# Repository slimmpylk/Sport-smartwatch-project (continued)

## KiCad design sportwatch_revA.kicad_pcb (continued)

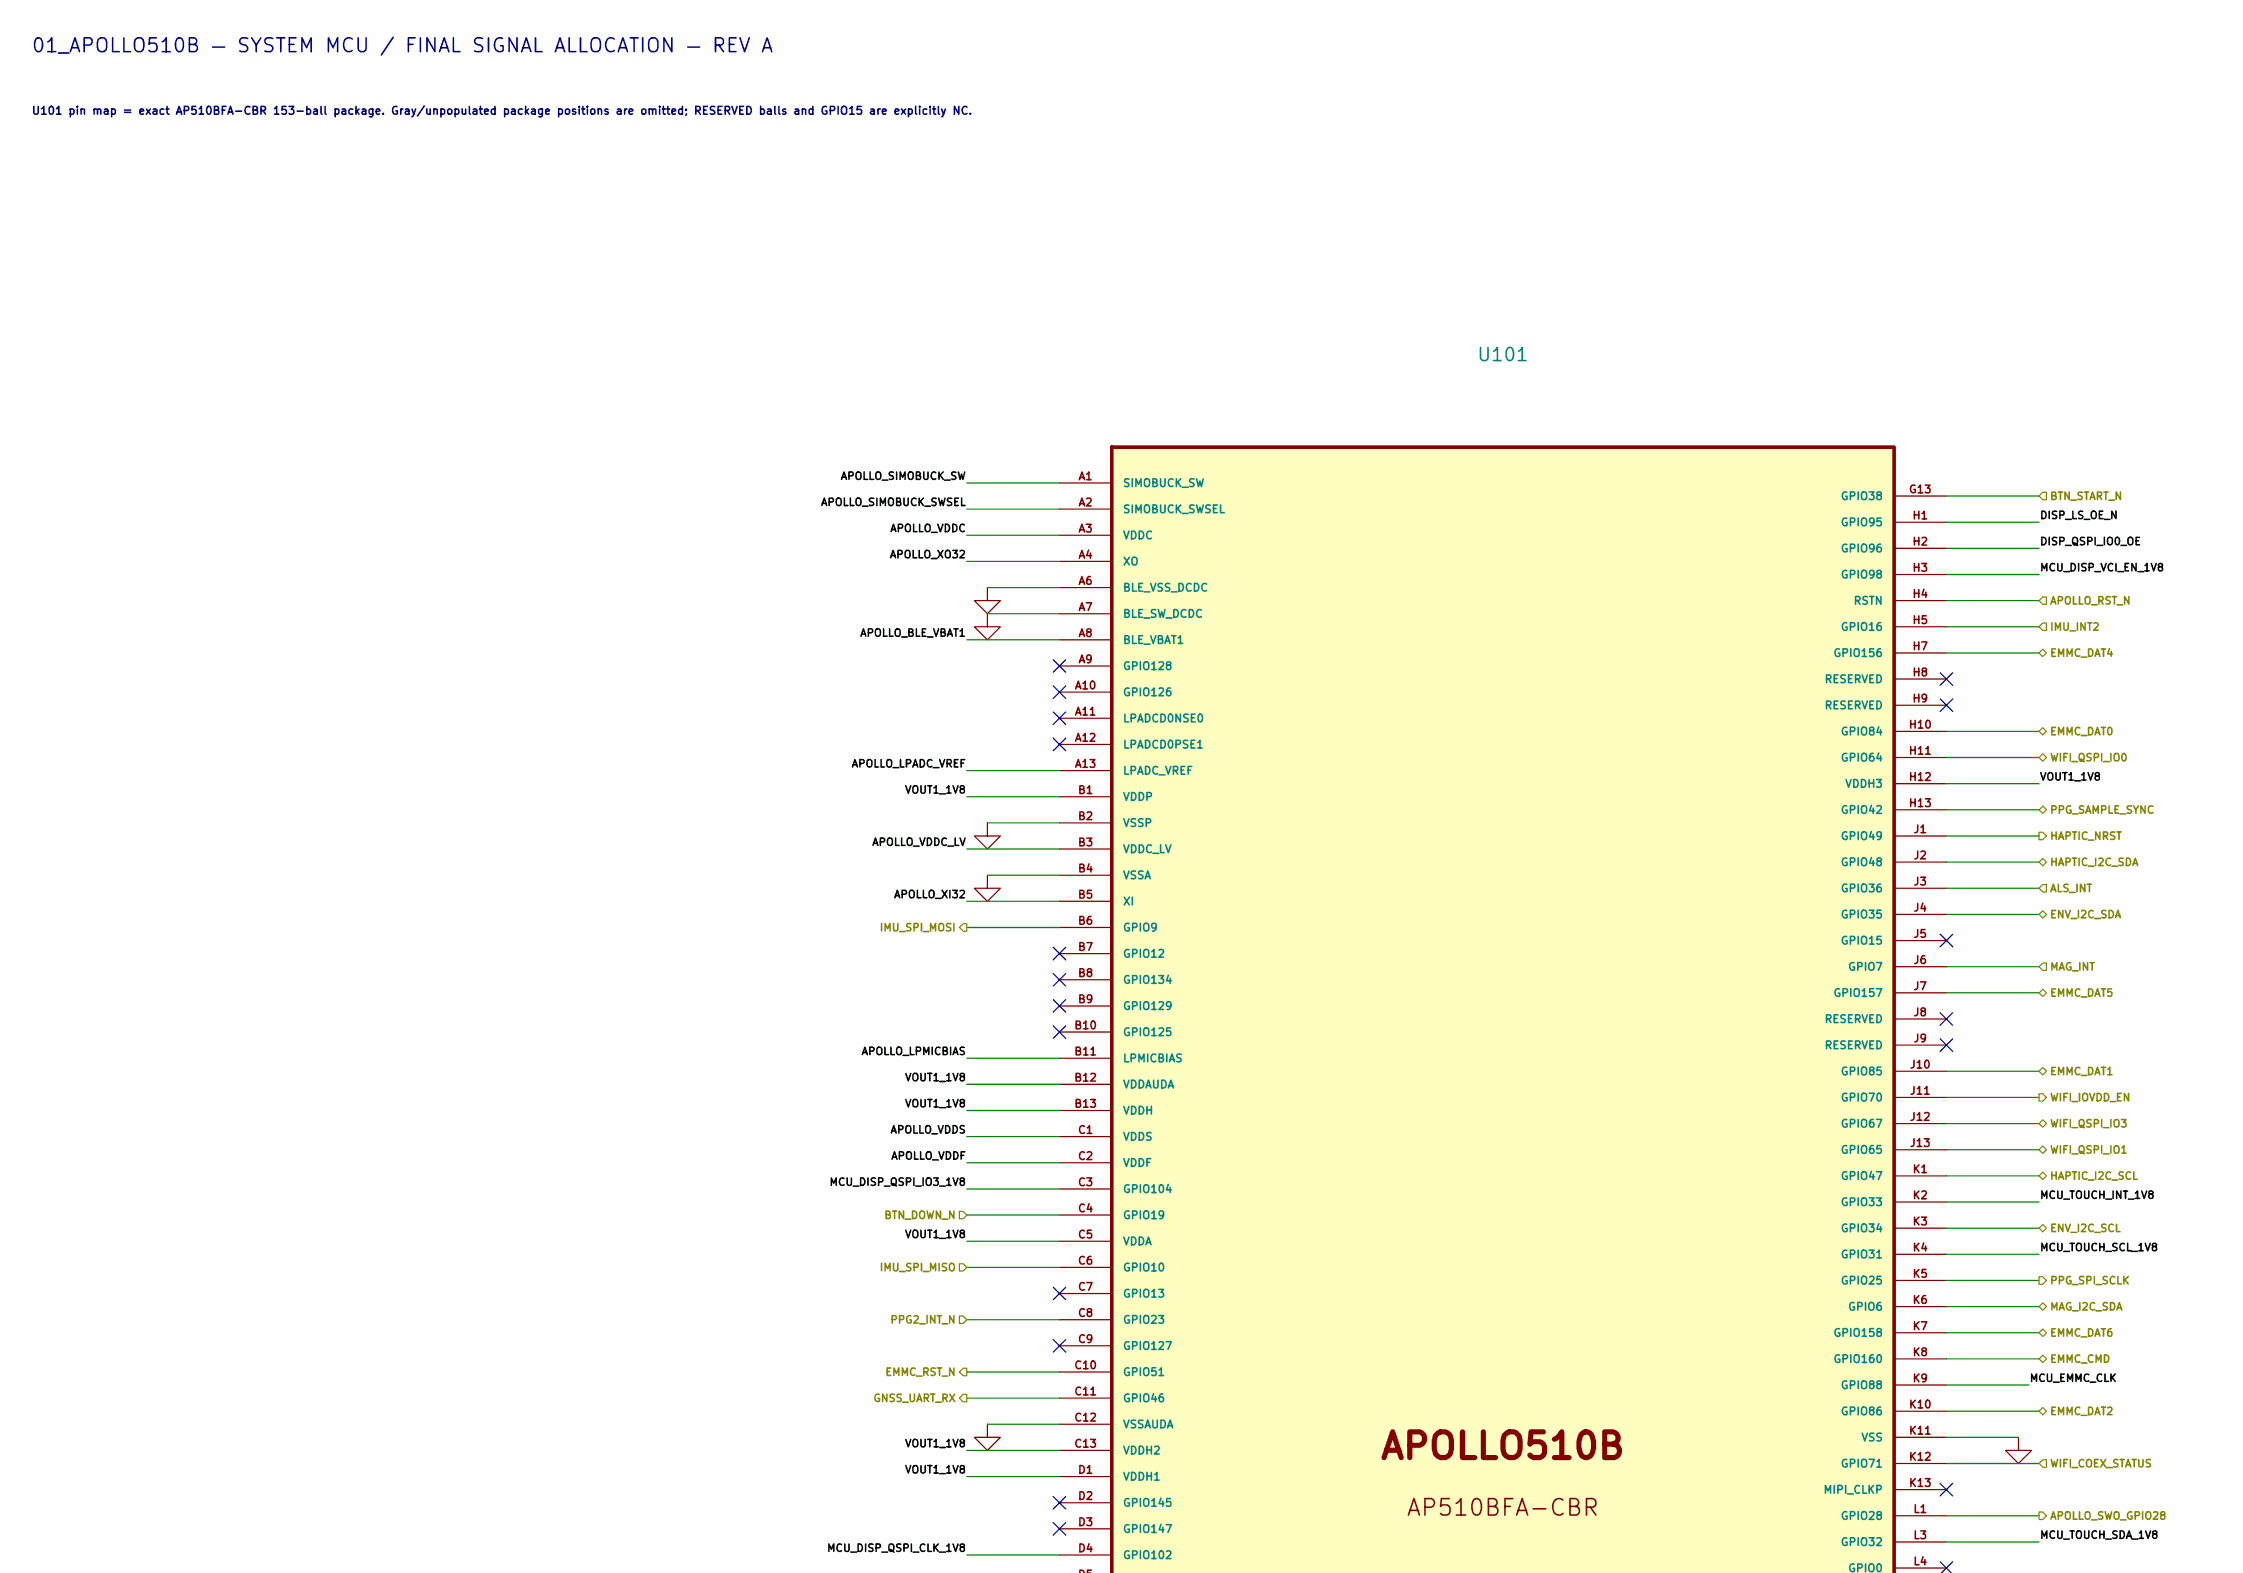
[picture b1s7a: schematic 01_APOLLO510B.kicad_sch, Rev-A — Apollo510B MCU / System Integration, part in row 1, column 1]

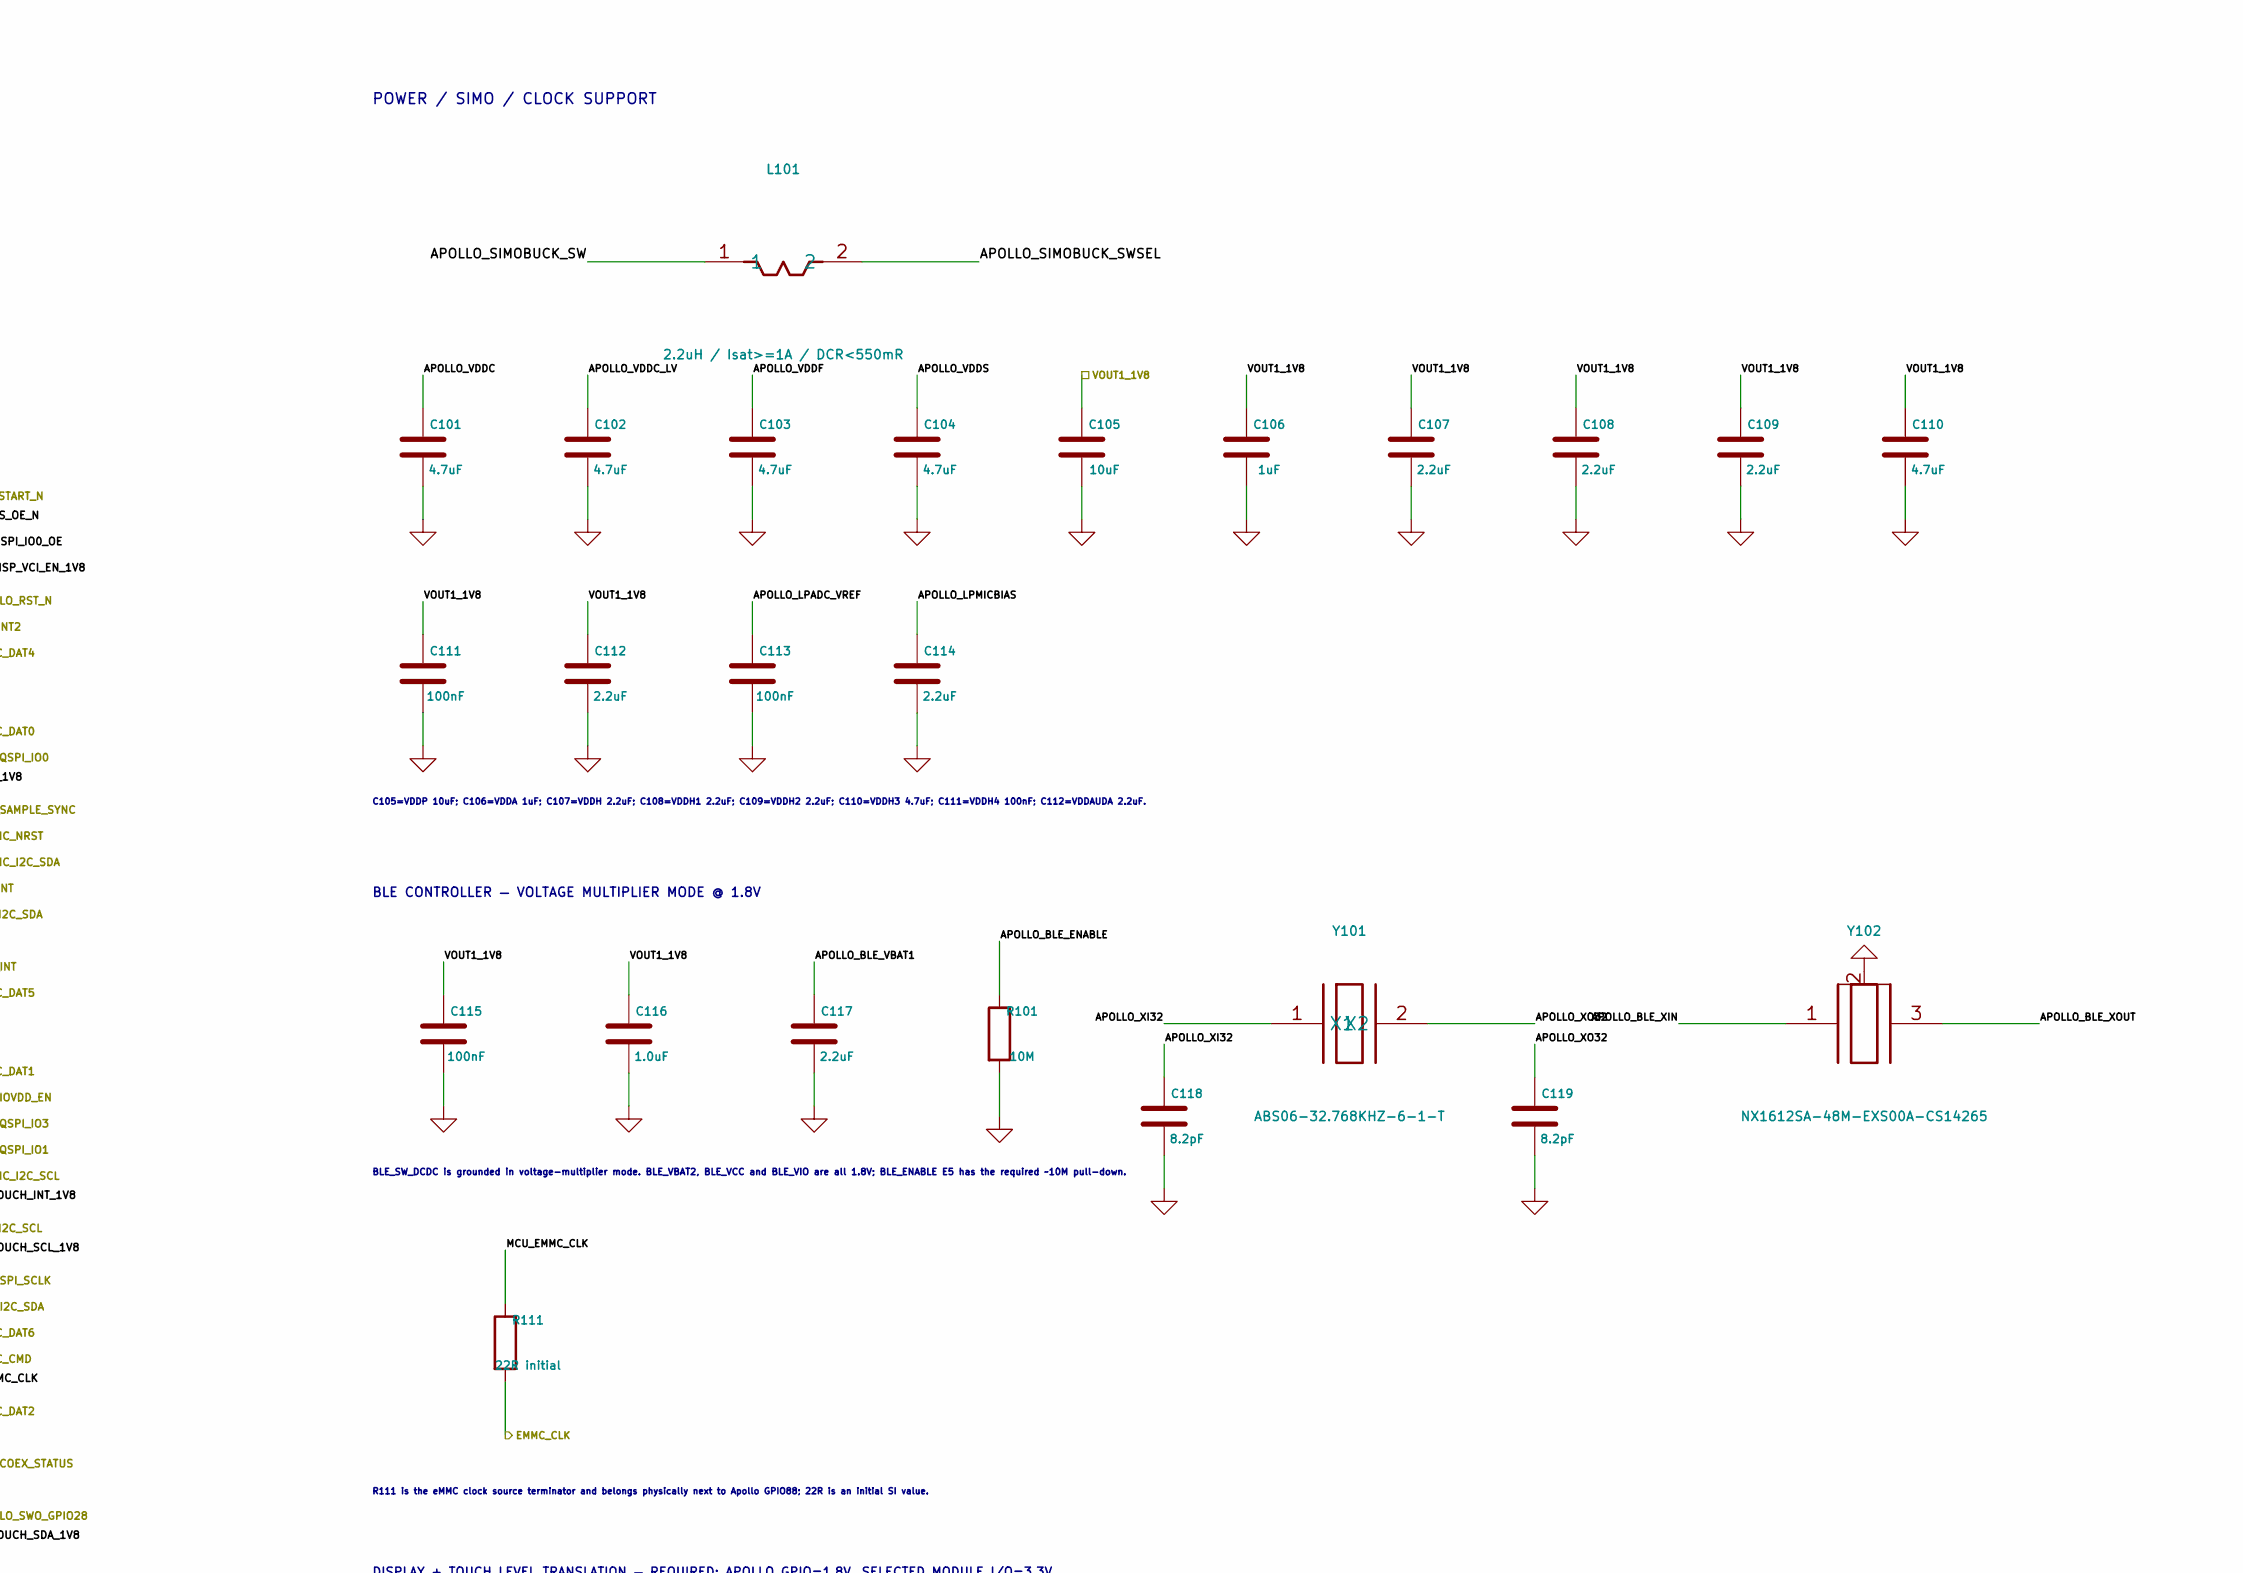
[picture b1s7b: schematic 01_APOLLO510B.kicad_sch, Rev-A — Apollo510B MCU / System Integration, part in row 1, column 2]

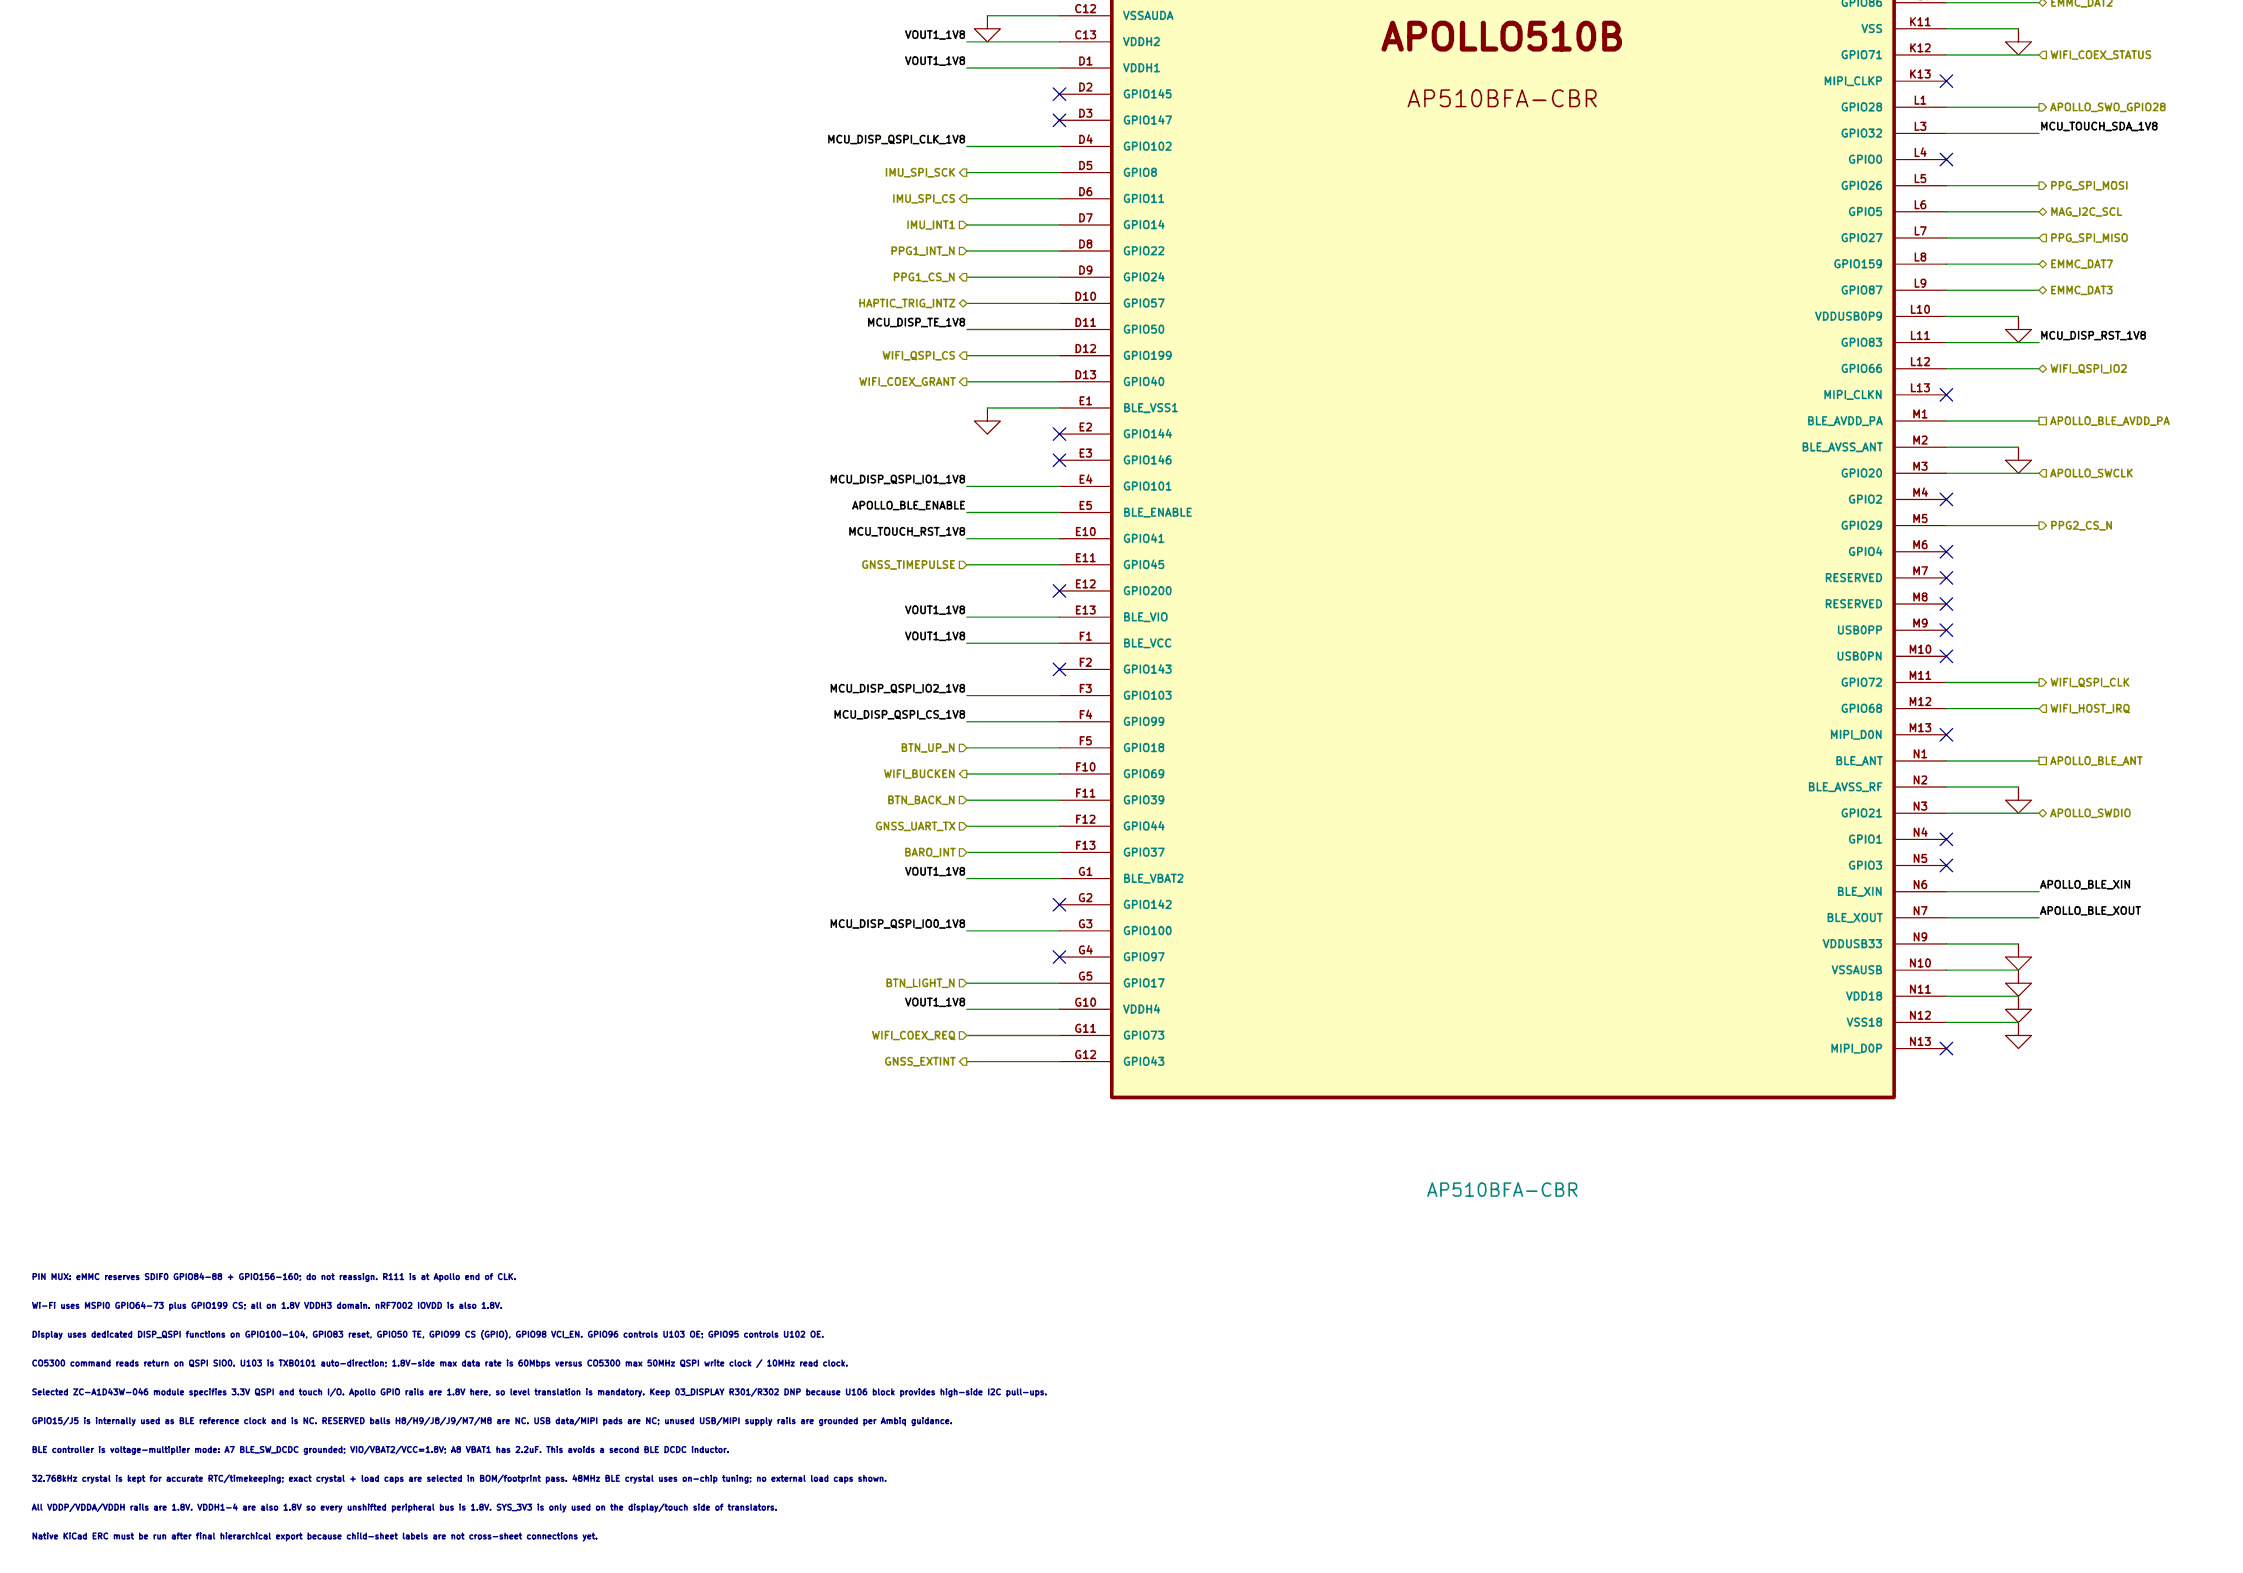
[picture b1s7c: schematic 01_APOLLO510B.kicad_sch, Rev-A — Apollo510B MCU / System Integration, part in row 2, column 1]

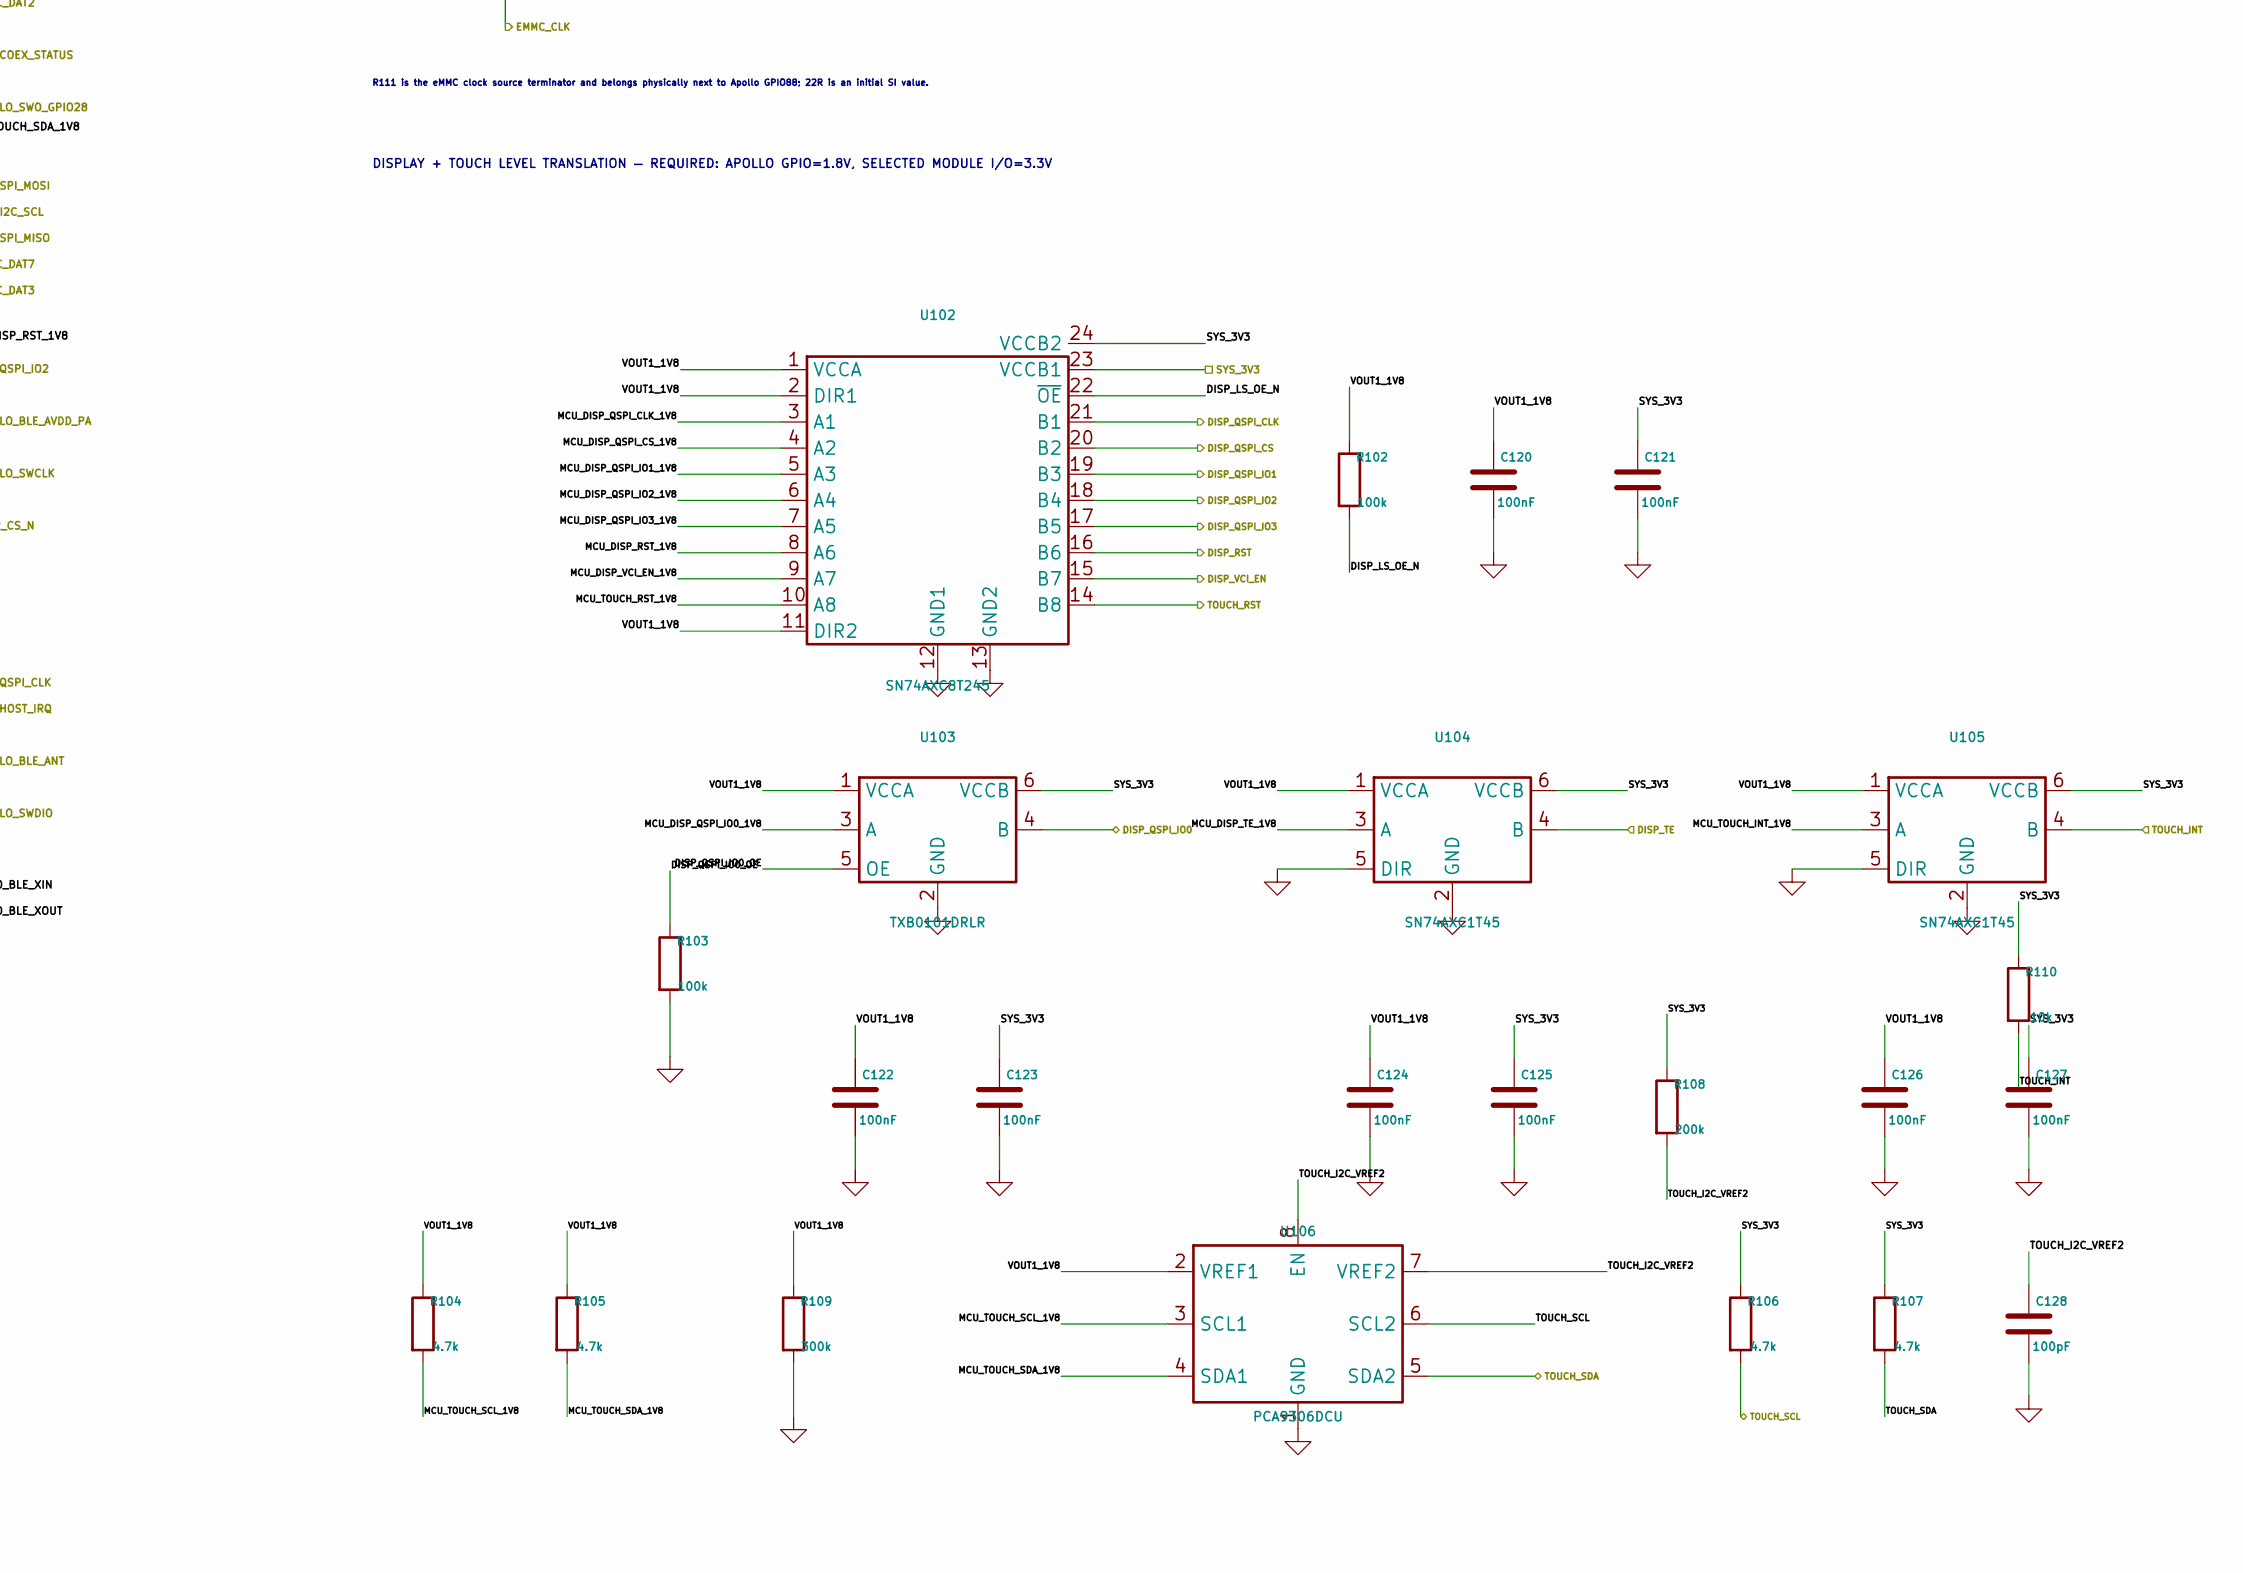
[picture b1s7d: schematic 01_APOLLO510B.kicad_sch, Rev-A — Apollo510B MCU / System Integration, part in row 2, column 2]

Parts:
C101, C102, C103, C104: 4.7uF; C_0201_0603Metric
C105: 10uF; C_0402_1005Metric
C106: 1uF; C_0402_1005Metric
C107, C108, C109, C112, C114, C117: 2.2uF; C_0402_1005Metric
C110: 4.7uF; C_0402_1005Metric
C111, C113, C115, C120, C121, C122, C123, C124, C125, C126, C127: 100nF; C_0402_1005Metric
C116: 1.0uF; C_0402_1005Metric
C118, C119: 8.2pF; C_0201_0603Metric
C128: 100pF; C_0201_0603Metric
L101: 2.2uH / Isat>=1A / DCR<550mR; L_0603_1608Metric
R101: 10M; R_0402_1005Metric
R102, R103: 100k; R_0402_1005Metric
R104, R105, R106, R107: 4.7k; R_0402_1005Metric
R108: 200k; R_0402_1005Metric
R109: 300k; R_0402_1005Metric
R110: 10k; R_0402_1005Metric
R111: 22R initial; R_0201_0603Metric
U101: AP510BFA-CBR; BGA-153_5.6x5.6mm_Layout13x13_P0.4mm_Ball0.25mm_Pad0.22mm_N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
U102: SN74AXC8T245; Texas_RHL0024A
U103: TXB0101DRLR; SOT-563
U104, U105: SN74AXC1T45; SOT-563
U106: PCA9306DCU; VSSOP-8_2.3x2mm_P0.5mm
Y101: ABS06-32.768KHZ-6-1-T; Crystal_SMD_ABS06_2.0x1.2mm
Y102: NX1612SA-48M-EXS00A-CS14265; Crystal_1612-4Pin_1.6x1.2mm

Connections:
/01_APOLLO510B/APOLLO_BLE_ENABLE: R101.1, U101.E5 (BLE_ENABLE)
/01_APOLLO510B/APOLLO_BLE_VBAT1: C117.1, U101.A8 (BLE_VBAT1)
/01_APOLLO510B/APOLLO_BLE_XIN: U101.N6 (BLE_XIN), Y102.1
/01_APOLLO510B/APOLLO_BLE_XOUT: U101.N7 (BLE_XOUT), Y102.3
/01_APOLLO510B/APOLLO_LPADC_VREF: C113.1, U101.A13 (LPADC_VREF)
/01_APOLLO510B/APOLLO_LPMICBIAS: C114.1, U101.B11 (LPMICBIAS)
/01_APOLLO510B/APOLLO_SIMOBUCK_SW: L101.1, U101.A1 (SIMOBUCK_SW)
/01_APOLLO510B/APOLLO_SIMOBUCK_SWSEL: L101.2, U101.A2 (SIMOBUCK_SWSEL)
/01_APOLLO510B/APOLLO_VDDC: C101.1, U101.A3 (VDDC)
/01_APOLLO510B/APOLLO_VDDC_LV: C102.1, U101.B3 (VDDC_LV)
/01_APOLLO510B/APOLLO_VDDF: C103.1, U101.C2 (VDDF)
/01_APOLLO510B/APOLLO_VDDS: C104.1, U101.C1 (VDDS)
/01_APOLLO510B/APOLLO_XI32: C118.1, U101.B5 (XI), Y101.1 (X1)
/01_APOLLO510B/APOLLO_XO32: C119.1, U101.A4 (XO), Y101.2 (X2)
/01_APOLLO510B/DISP_LS_OE_N: R102.2, U101.H1 (GPIO95), U102.22 (~OE)
/01_APOLLO510B/DISP_QSPI_IO0_OE: R103.1, U101.H2 (GPIO96), U103.5 (OE)
/01_APOLLO510B/MCU_DISP_QSPI_CLK_1V8: U101.D4 (GPIO102), U102.3 (A1)
/01_APOLLO510B/MCU_DISP_QSPI_CS_1V8: U101.F4 (GPIO99), U102.4 (A2)
/01_APOLLO510B/MCU_DISP_QSPI_IO0_1V8: U101.G3 (GPIO100), U103.3 (A)
/01_APOLLO510B/MCU_DISP_QSPI_IO1_1V8: U101.E4 (GPIO101), U102.5 (A3)
/01_APOLLO510B/MCU_DISP_QSPI_IO2_1V8: U101.F3 (GPIO103), U102.6 (A4)
/01_APOLLO510B/MCU_DISP_QSPI_IO3_1V8: U101.C3 (GPIO104), U102.7 (A5)
/01_APOLLO510B/MCU_DISP_RST_1V8: U101.L11 (GPIO83), U102.8 (A6)
/01_APOLLO510B/MCU_DISP_TE_1V8: U101.D11 (GPIO50), U104.3 (A)
/01_APOLLO510B/MCU_DISP_VCI_EN_1V8: U101.H3 (GPIO98), U102.9 (A7)
/01_APOLLO510B/MCU_EMMC_CLK: R111.1, U101.K9 (GPIO88)
/01_APOLLO510B/MCU_TOUCH_INT_1V8: U101.K2 (GPIO33), U105.3 (A)
/01_APOLLO510B/MCU_TOUCH_RST_1V8: U101.E10 (GPIO41), U102.10 (A8)
/01_APOLLO510B/MCU_TOUCH_SCL_1V8: R104.2, U101.K4 (GPIO31), U106.3 (SCL1)
/01_APOLLO510B/MCU_TOUCH_SDA_1V8: R105.2, U101.L3 (GPIO32), U106.4 (SDA1)
/01_APOLLO510B/TOUCH_I2C_VREF2: C128.1, R108.2, U106.7 (VREF2), U106.8 (EN)
/APOLLO_BLE_ANT: U101.N1 (BLE_ANT); also elsewhere on the board
/APOLLO_BLE_AVDD_PA: U101.M1 (BLE_AVDD_PA); also elsewhere on the board
/APOLLO_RST_N: U101.H4 (RSTN); also elsewhere on the board
/APOLLO_SWCLK: U101.M3 (GPIO20); also elsewhere on the board
/APOLLO_SWDIO: U101.N3 (GPIO21); also elsewhere on the board
/APOLLO_SWO_GPIO28: U101.L1 (GPIO28); also elsewhere on the board
/BTN_BACK_N: U101.F11 (GPIO39); also elsewhere on the board
/BTN_DOWN_N: U101.C4 (GPIO19); also elsewhere on the board
/BTN_LIGHT_N: U101.G5 (GPIO17); also elsewhere on the board
/BTN_START_N: U101.G13 (GPIO38); also elsewhere on the board
/BTN_UP_N: U101.F5 (GPIO18); also elsewhere on the board
/DISP_QSPI_CLK: U102.21 (B1); also elsewhere on the board
/DISP_QSPI_CS: U102.20 (B2); also elsewhere on the board
/DISP_QSPI_IO0: U103.4 (B); also elsewhere on the board
/DISP_QSPI_IO1: U102.19 (B3); also elsewhere on the board
/DISP_QSPI_IO2: U102.18 (B4); also elsewhere on the board
/DISP_QSPI_IO3: U102.17 (B5); also elsewhere on the board
/DISP_RST: U102.16 (B6); also elsewhere on the board
/DISP_TE: U104.4 (B); also elsewhere on the board
/DISP_VCI_EN: U102.15 (B7); also elsewhere on the board
/EMMC_CLK: R111.2; also elsewhere on the board
/EMMC_CMD: U101.K8 (GPIO160); also elsewhere on the board
/EMMC_DAT0: U101.H10 (GPIO84); also elsewhere on the board
/EMMC_DAT1: U101.J10 (GPIO85); also elsewhere on the board
/EMMC_DAT2: U101.K10 (GPIO86); also elsewhere on the board
/EMMC_DAT3: U101.L9 (GPIO87); also elsewhere on the board
/EMMC_DAT4: U101.H7 (GPIO156); also elsewhere on the board
/EMMC_DAT5: U101.J7 (GPIO157); also elsewhere on the board
/EMMC_DAT6: U101.K7 (GPIO158); also elsewhere on the board
/EMMC_DAT7: U101.L8 (GPIO159); also elsewhere on the board
/EMMC_RST_N: U101.C10 (GPIO51); also elsewhere on the board
/GNSS_EXTINT: U101.G12 (GPIO43); also elsewhere on the board
/GNSS_TIMEPULSE: U101.E11 (GPIO45); also elsewhere on the board
/GNSS_UART_RX: U101.C11 (GPIO46); also elsewhere on the board
/GNSS_UART_TX: U101.F12 (GPIO44); also elsewhere on the board
/HAPTIC_I2C_SCL: U101.K1 (GPIO47); also elsewhere on the board
/HAPTIC_I2C_SDA: U101.J2 (GPIO48); also elsewhere on the board
/HAPTIC_NRST: U101.J1 (GPIO49); also elsewhere on the board
/HAPTIC_TRIG_INTZ: U101.D10 (GPIO57); also elsewhere on the board
/IMU_INT1: U101.D7 (GPIO14); also elsewhere on the board
/IMU_INT2: U101.H5 (GPIO16); also elsewhere on the board
/IMU_SPI_CS: U101.D6 (GPIO11); also elsewhere on the board
/IMU_SPI_MISO: U101.C6 (GPIO10); also elsewhere on the board
/IMU_SPI_MOSI: U101.B6 (GPIO9); also elsewhere on the board
/IMU_SPI_SCK: U101.D5 (GPIO8); also elsewhere on the board
/MAG_I2C_SCL: U101.L6 (GPIO5); also elsewhere on the board
/MAG_I2C_SDA: U101.K6 (GPIO6); also elsewhere on the board
/MAG_INT: U101.J6 (GPIO7); also elsewhere on the board
/SYS_3V3: C121.1, C123.1, C125.1, C127.1, R106.1, R107.1, R108.1, R110.1, U102.23 (VCCB1), U102.24 (VCCB2), U103.6 (VCCB), U104.6 (VCCB), U105.6 (VCCB); also elsewhere on the board
/TOUCH_INT: R110.2, U105.4 (B); also elsewhere on the board
/TOUCH_RST: U102.14 (B8); also elsewhere on the board
/TOUCH_SCL: R106.2, U106.6 (SCL2); also elsewhere on the board
/TOUCH_SDA: R107.2, U106.5 (SDA2); also elsewhere on the board
/WIFI_BUCKEN: U101.F10 (GPIO69); also elsewhere on the board
/WIFI_COEX_GRANT: U101.D13 (GPIO40); also elsewhere on the board
/WIFI_COEX_REQ: U101.G11 (GPIO73); also elsewhere on the board
/WIFI_COEX_STATUS: U101.K12 (GPIO71); also elsewhere on the board
/WIFI_HOST_IRQ: U101.M12 (GPIO68); also elsewhere on the board
/WIFI_IOVDD_EN: U101.J11 (GPIO70); also elsewhere on the board
/WIFI_QSPI_CLK: U101.M11 (GPIO72); also elsewhere on the board
/WIFI_QSPI_CS: U101.D12 (GPIO199); also elsewhere on the board
/WIFI_QSPI_IO0: U101.H11 (GPIO64); also elsewhere on the board
/WIFI_QSPI_IO1: U101.J13 (GPIO65); also elsewhere on the board
/WIFI_QSPI_IO2: U101.L12 (GPIO66); also elsewhere on the board
/WIFI_QSPI_IO3: U101.J12 (GPIO67); also elsewhere on the board
ALS_INT: U101.J3 (GPIO36); also elsewhere on the board
BARO_INT: U101.F13 (GPIO37); also elsewhere on the board
ENV_I2C_SCL: U101.K3 (GPIO34); also elsewhere on the board
ENV_I2C_SDA: U101.J4 (GPIO35); also elsewhere on the board
GND: C101.2, C102.2, C103.2, C104.2, C105.2, C106.2, C107.2, C108.2, C109.2, C110.2, C111.2, C112.2, C113.2, C114.2, C115.2, C116.2, C117.2, C118.2, C119.2, C120.2, C121.2, C122.2, C123.2, C124.2, C125.2, C126.2, C127.2, C128.2, R101.2, R103.2, R109.2, U101.A6 (BLE_VSS_DCDC), U101.A7 (BLE_SW_DCDC), U101.B2 (VSSP), U101.B4 (VSSA), U101.C12 (VSSAUDA), U101.E1 (BLE_VSS1), U101.K11 (VSS), U101.L10 (VDDUSB0P9), U101.M2 (BLE_AVSS_ANT), U101.N2 (BLE_AVSS_RF), U101.N9 (VDDUSB33), U101.N10 (VSSAUSB), U101.N11 (VDD18), U101.N12 (VSS18), U102.12 (GND1), U102.13 (GND2), U103.2 (GND), U104.2 (GND), U104.5 (DIR), U105.2 (GND), U105.5 (DIR), U106.1 (GND), Y102.2 (GND), Y102.4 (GND); also elsewhere on the board
PPG1_CS_N: U101.D9 (GPIO24)
PPG1_INT_N: U101.D8 (GPIO22)
PPG2_CS_N: U101.M5 (GPIO29)
PPG2_INT_N: U101.C8 (GPIO23)
PPG_SAMPLE_SYNC: U101.H13 (GPIO42)
PPG_SPI_MISO: U101.L7 (GPIO27)
PPG_SPI_MOSI: U101.L5 (GPIO26)
PPG_SPI_SCLK: U101.K5 (GPIO25)
VOUT1_1V8: C105.1, C106.1, C107.1, C108.1, C109.1, C110.1, C111.1, C112.1, C115.1, C116.1, C120.1, C122.1, C124.1, C126.1, R102.1, R104.1, R105.1, R109.1, U101.B1 (VDDP), U101.B12 (VDDAUDA), U101.B13 (VDDH), U101.C5 (VDDA), U101.C13 (VDDH2), U101.D1 (VDDH1), U101.E13 (BLE_VIO), U101.F1 (BLE_VCC), U101.G1 (BLE_VBAT2), U101.G10 (VDDH4), U101.H12 (VDDH3), U102.1 (VCCA), U102.2 (DIR1), U102.11 (DIR2), U103.1 (VCCA), U104.1 (VCCA), U105.1 (VCCA), U106.2 (VREF1); also elsewhere on the board

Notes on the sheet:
01_APOLLO510B — SYSTEM MCU / FINAL SIGNAL ALLOCATION — REV A
Selected ZC-A1D43W-046 module specifies 3.3V QSPI and touch I/O. Apollo GPIO rails are 1.8V here, so level translation is mandatory. Keep 03_DISPLAY R301/R302 DNP because U106 block provides high-side I2C pull-ups.
32.768kHz crystal is kept for accurate RTC/timekeeping; exact crystal + load caps are selected in BOM/footprint pass. 48MHz BLE crystal uses on-chip tuning; no external load caps shown.
DISPLAY + TOUCH LEVEL TRANSLATION — REQUIRED: APOLLO GPIO=1.8V, SELECTED MODULE I/O=3.3V
Native KiCad ERC must be run after final hierarchical export because child-sheet labels are not cross-sheet connections yet.
POWER / SIMO / CLOCK SUPPORT
BLE CONTROLLER — VOLTAGE MULTIPLIER MODE @ 1.8V
GPIO15/J5 is internally used as BLE reference clock and is NC. RESERVED balls H8/H9/J8/J9/M7/M8 are NC. USB data/MIPI pads are NC; unused USB/MIPI supply rails are grounded per Ambiq guidance.
BLE controller is voltage-multiplier mode: A7 BLE_SW_DCDC grounded; VIO/VBAT2/VCC=1.8V; A8 VBAT1 has 2.2uF. This avoids a second BLE DCDC inductor.
Wi-Fi uses MSPI0 GPIO64-73 plus GPIO199 CS; all on 1.8V VDDH3 domain. nRF7002 IOVDD is also 1.8V.
Display uses dedicated DISP_QSPI functions on GPIO100-104, GPIO83 reset, GPIO50 TE, GPIO99 CS (GPIO), GPIO98 VCI_EN. GPIO96 controls U103 OE; GPIO95 controls U102 OE.
U101 pin map = exact AP510BFA-CBR 153-ball package. Gray/unpopulated package positions are omitted; RESERVED balls and GPIO15 are explicitly NC.
All VDDP/VDDA/VDDH rails are 1.8V. VDDH1-4 are also 1.8V so every unshifted peripheral bus is 1.8V. SYS_3V3 is only used on the display/touch side of translators.
CO5300 command reads return on QSPI SIO0. U103 is TXB0101 auto-direction; 1.8V-side max data rate is 60Mbps versus CO5300 max 50MHz QSPI write clock / 10MHz read clock.
BLE_SW_DCDC is grounded in voltage-multiplier mode. BLE_VBAT2, BLE_VCC and BLE_VIO are all 1.8V; BLE_ENABLE E5 has the required ~10M pull-down.
R111 is the eMMC clock source terminator and belongs physically next to Apollo GPIO88; 22R is an initial SI value.
PIN MUX: eMMC reserves SDIF0 GPIO84-88 + GPIO156-160; do not reassign. R111 is at Apollo end of CLK.
C105=VDDP 10uF; C106=VDDA 1uF; C107=VDDH 2.2uF; C108=VDDH1 2.2uF; C109=VDDH2 2.2uF; C110=VDDH3 4.7uF; C111=VDDH4 100nF; C112=VDDAUDA 2.2uF.
